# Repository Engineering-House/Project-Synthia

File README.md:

# Project Synthia
Project Synthia is a digital synthesizer that is designed based upon the Suzuki Omnichord. This repository contains the firmware code for the microcontroller as well as the hardware schematics.

# Project Synthia Firmware

A brief description of what this firmware does, the target application, and the primary protocol used (e.g., "An ESP32-based firmware for monitoring soil moisture via MQTT").

## Hardware Requirements

* **Microcontroller:** [e.g., STM32F405RG / ESP32-WROOM-32E]
* **Development Board/PCB:** NUCLEO-G431KB
* **External Peripherals:** 
* **Debugger/Programmer:**

### Pin Mapping
The pins are mapped to the following variable values. It is currently understood that on the NUCLEO-G431KB, the PB9 pin does not exist.

| Variable | Pin | Pin Type | IO |
| :--- | :--- | :--- | :--- |
| majorChords | PA7 | GPIO | Output |
| minorChords | PB0 | GPIO | Output |
| seventhChords | PA9 | GPIO | Output |
| DAC_0 | PF0 | GPIO | Output |
| DAC_1 | PF1 | GPIO | Output |
| DAC_2 | PA8 | GPIO | Output |
| DAC_3 | PA0 | GPIO | Output |
| DAC_4 | PA1 | GPIO | Output |
| DAC_5 | PA4 | GPIO | Output |
| DAC_6 | PA5 | GPIO | Output |
| DAC_7 | PA6 | GPIO | Output |
| tempoControl | PB9 | Analog | Input |
| rhythmSwitch | PA10 | GPIO | Input |
| rhythmMatrix[4] | PA11 | GPIO | Input |
| fontSwitch | PA12 | GPIO | Input |
| fontMatrix[4] | PA15 | GPIO | Input |
| chordMatrix_0 | PB4 | GPIO | Input |
| chordMatrix_1 | PB5 | GPIO | Input |
| chordMatrix_2 | PB6 | GPIO | Input |
| chordMatrix_3 | PB7 | GPIO | Input |

## Getting Started

### Prerequisites & Toolchain
* **IDE/Framework:** STM32CubeIDE, STM32CubeMX
* **Compiler:** 
* **Dependencies:** N/A

### Building the Firmware
```bash
# Clone the repository
git clone https://github.com/Engineering-House/Project-Synthia.git
cd Project-Synthia/Synthia-Firmware
```

In the STM32CubeIDE, after opening the firmware folder detailed above, clean and build the project from the Project menu.

##  Flashing & Debugging

There is currently no flashing and debugging process. Please update this when needed.

## Configuration

Explain how users can modify settings before compiling (e.g., Wi-Fi credentials, baud rates, calibration constants).
* **Configuration File:** 
* **Key Parameters:**
## Testing & Debugging

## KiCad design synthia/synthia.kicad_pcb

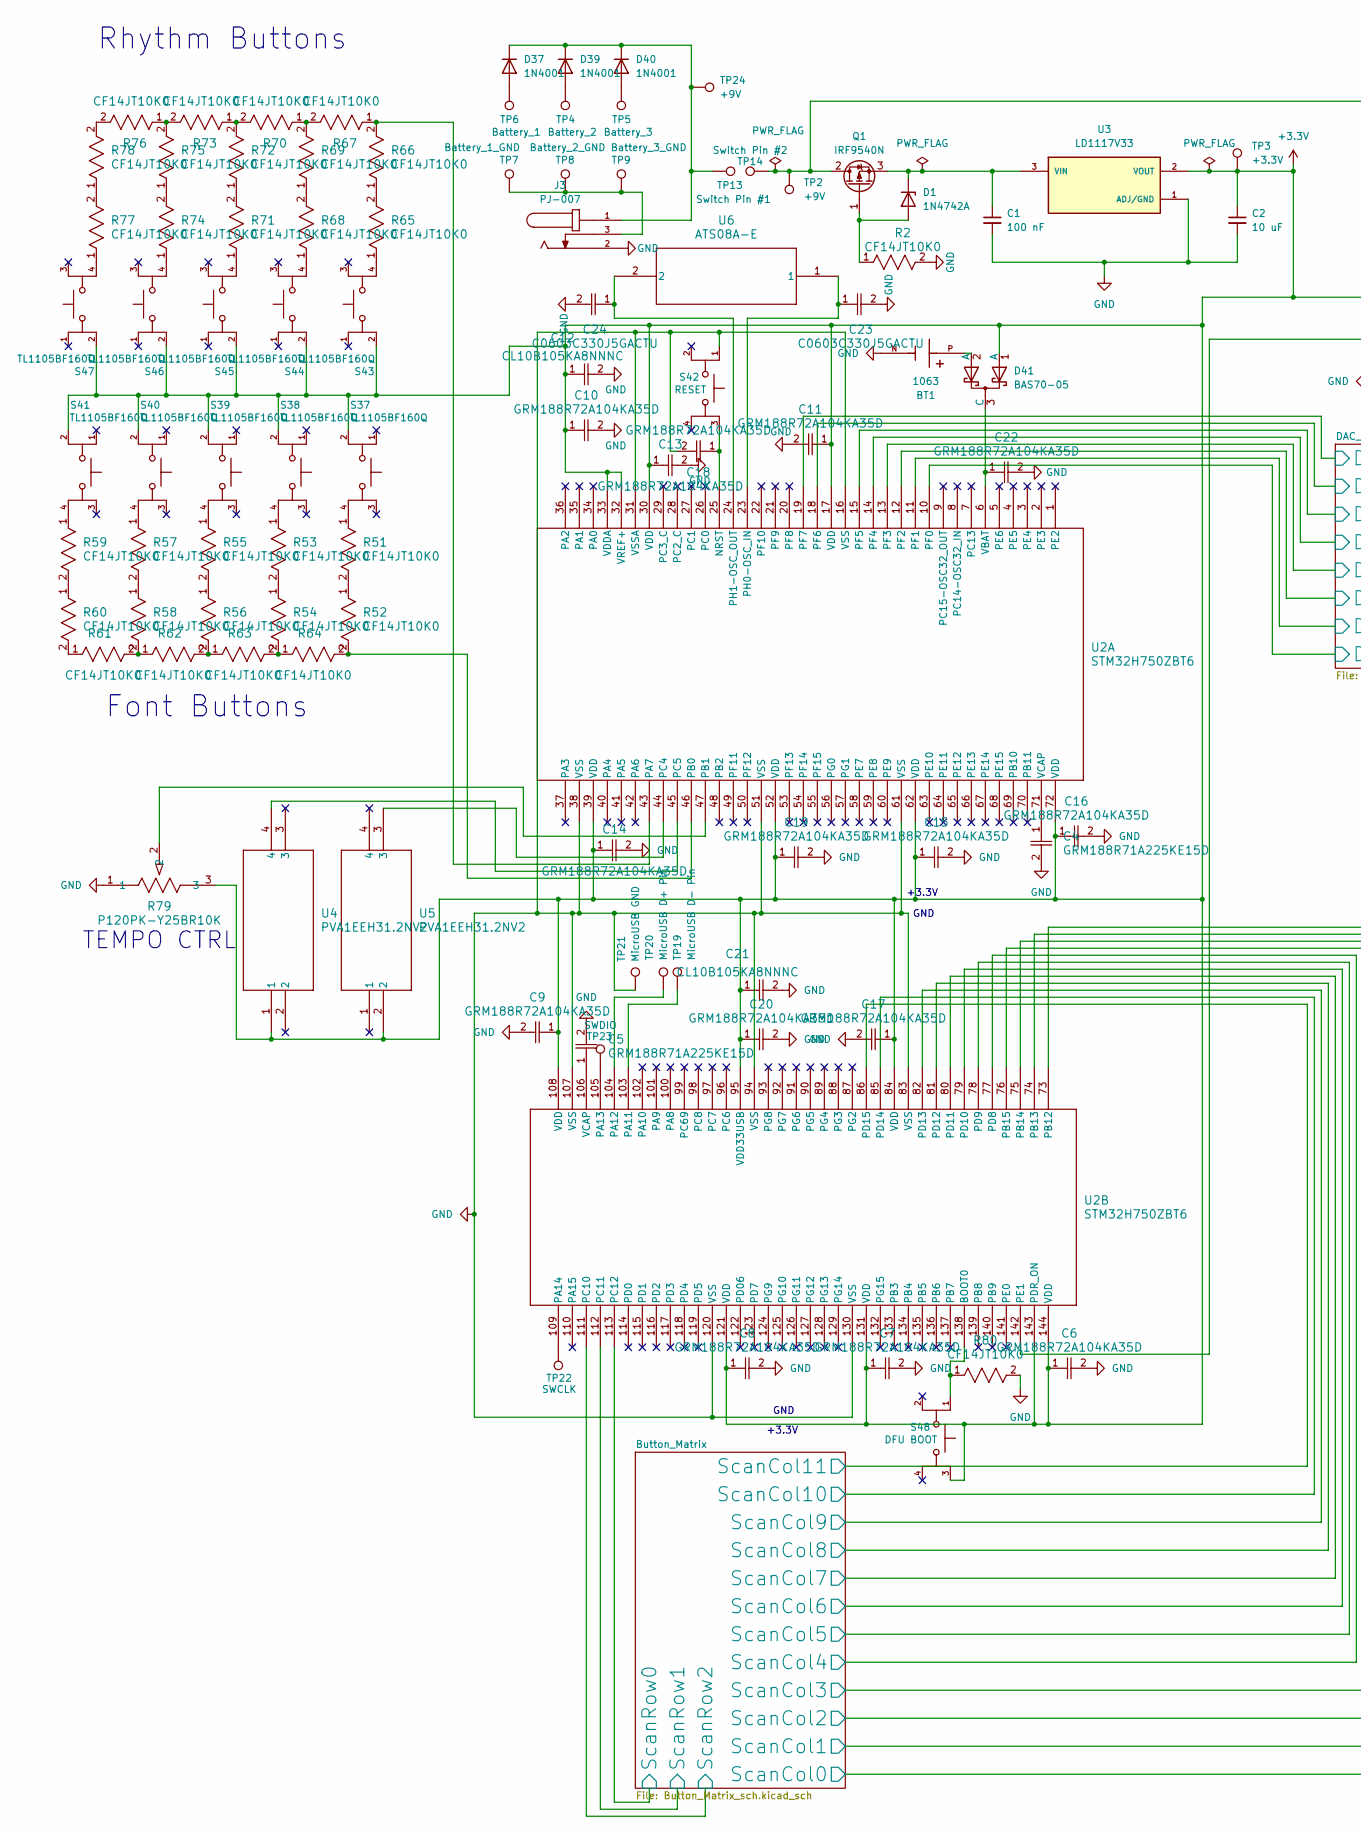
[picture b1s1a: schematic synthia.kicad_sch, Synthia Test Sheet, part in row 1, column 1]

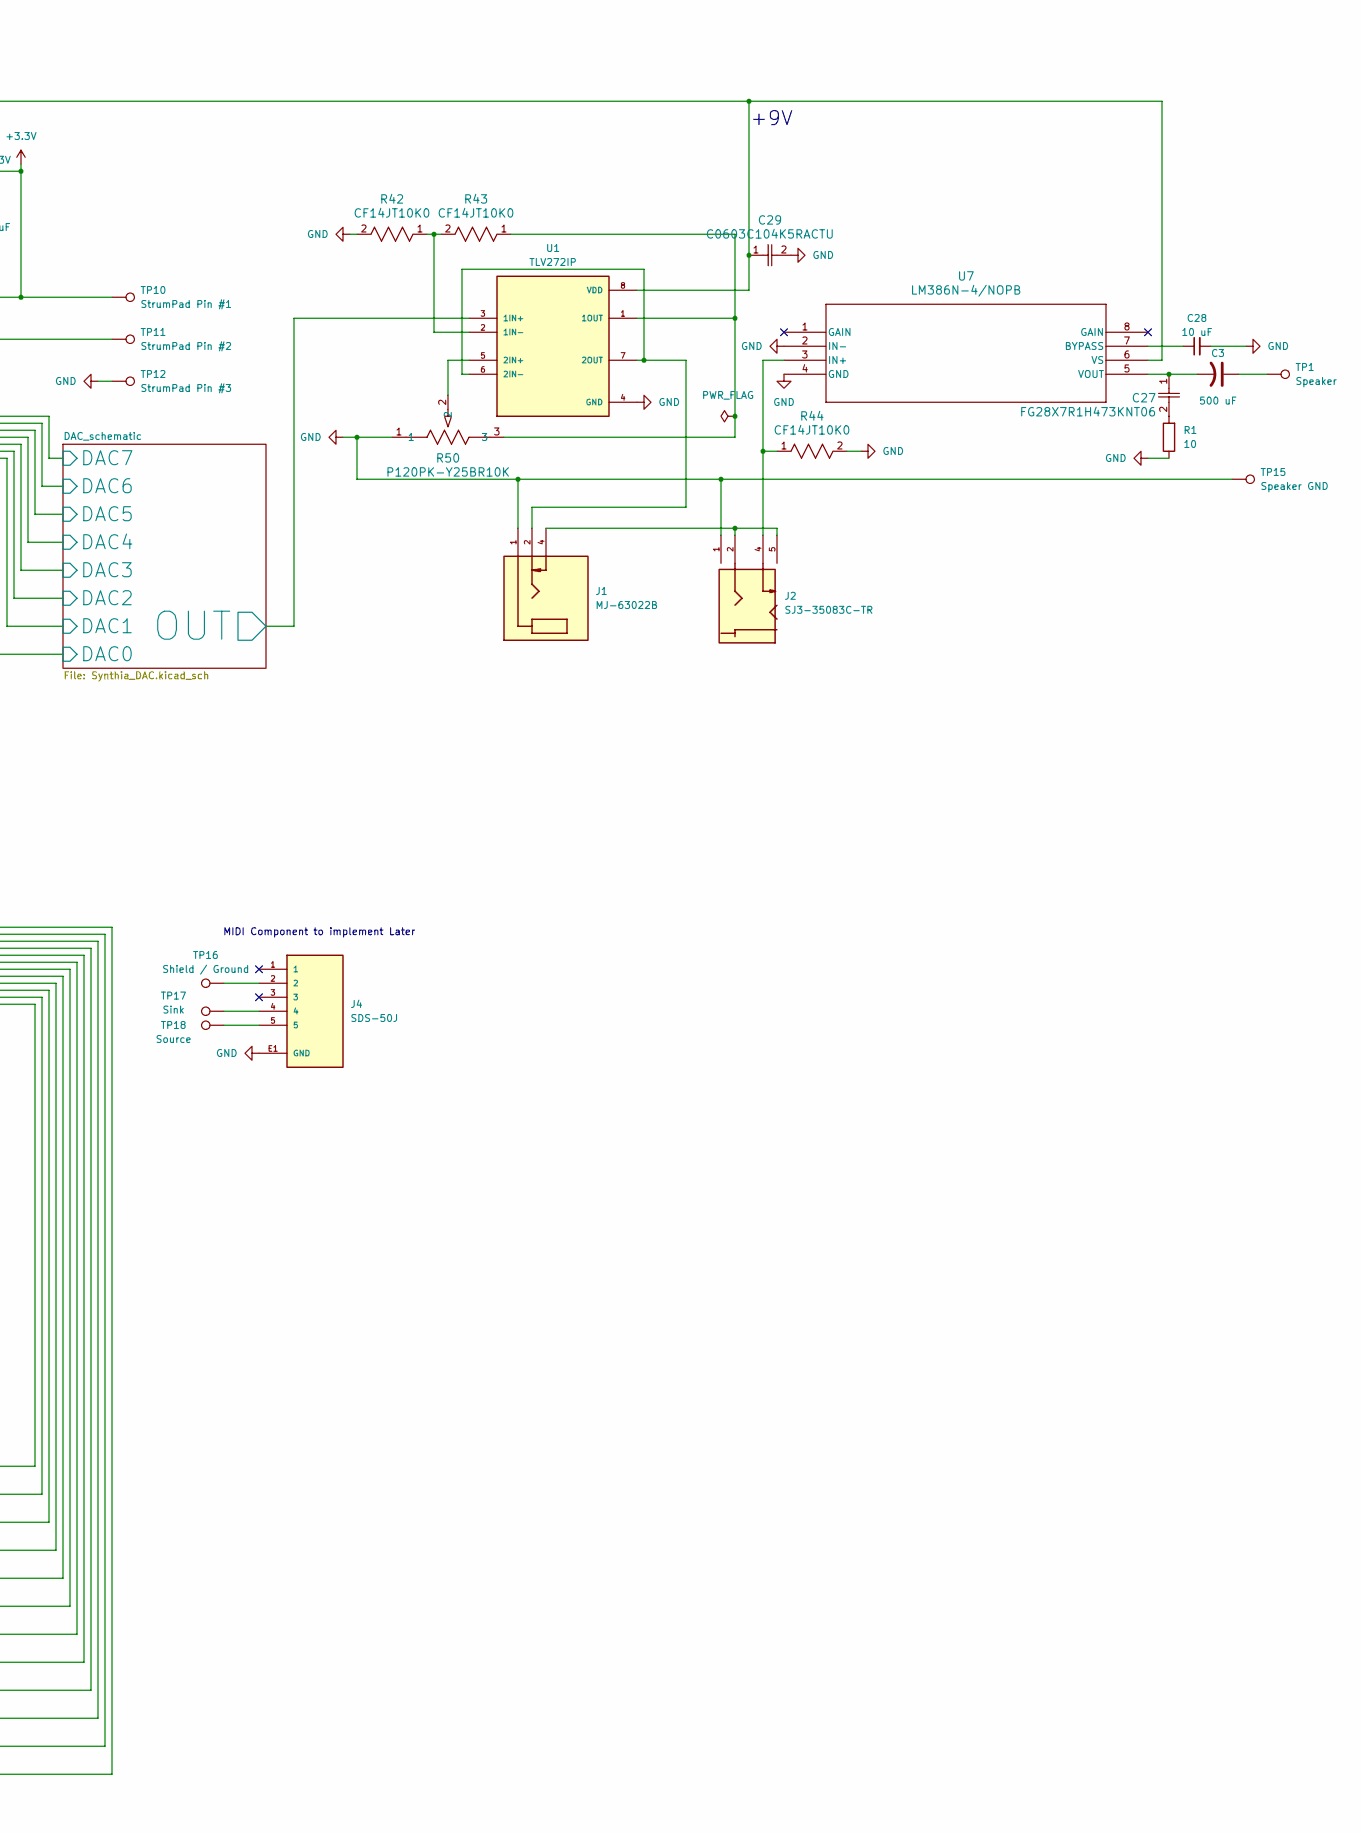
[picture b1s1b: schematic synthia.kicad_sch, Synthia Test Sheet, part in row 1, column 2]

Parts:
BT1: 1063; BAT_1063; PARTREV F
C1: 100 nF; CP_Radial_Tantal_D5.0mm_P5.00mm
C2, C28: 10 uF; CP_Radial_Tantal_D5.0mm_P5.00mm
C3: 500 uF; CP_Radial_Tantal_D5.0mm_P5.00mm
C4, C5: GRM188R71A225KE15D; G-188_MUR
C6, C7, C8, C9, C10, C11, C13, C14, C15, C16, C17, C18, C19, C20, C22: GRM188R72A104KA35D
C12, C21: CL10B105KA8NNNC; CAP_CL10_SAM-L
C23, C24: C0603C330J5GACTU; CAPC17595_87N_KEM-L
C27: FG28X7R1H473KNT06; CAP_FG28_TDK
C29: C0603C104K5RACTU; CAPC17595_95N_KEM-L
D1: 1N4742A; D_DO-41_SOD81_P10.16mm_Horizontal
D37, D39, D40: 1N4001; D_DO-41_SOD81_P10.16mm_Horizontal
D41: BAS70-05; P200_SOT-23
J1: MJ-63022B; CUI_MJ-63022B; PARTREV 1.0
J2: SJ3-35083C-TR; SAMESKY_SJ3-35083C-TR; PARTREV 1.01
J3: PJ-007; SAMESKY_PJ-007; PARTREV 1.07
J4: SDS-50J; CUI_SDS-50J; PARTREV 1.06/02-13-2020
Q1: IRF9540N; TO-220-3_Vertical
R1: 10; STA_CF14_STP
R2, R42, R43, R44, R51, R52, R53, R54, R55, R56, R57, R58, R59, R60, R61, R62, R63, R64, R65, R66, R67, R68, R69, R70, R71, R72, R73, R74, R75, R76, R77, R78, R80: CF14JT10K0; STA_CF14_STP
R50, R79: P120PK-Y25BR10K; POT_P120PK-x25_TTE
S37, S38, S39, S40, S41, S43, S44, S45, S46, S47: TL1105BF160Q; SW_TL1105BF160Q; PARTREV A
S42: RESET; SW_TL1105BF160Q; PARTREV A
S48: DFU BOOT; SW_TL1105BF160Q; PARTREV A
TP1: Speaker; TestPoint_Plated_Hole_D2.0mm
TP2, TP24: +9V; TestPoint_Pad_2.0x2.0mm
TP3: +3.3V; TestPoint_Pad_2.0x2.0mm
TP4: Battery_2; TestPoint_Plated_Hole_D2.0mm
TP5: Battery_3; TestPoint_Plated_Hole_D2.0mm
TP6: Battery_1; TestPoint_Plated_Hole_D2.0mm
TP7: Battery_1_GND; TestPoint_Plated_Hole_D2.0mm
TP8: Battery_2_GND; TestPoint_Plated_Hole_D2.0mm
TP9: Battery_3_GND; TestPoint_Plated_Hole_D2.0mm
TP10: StrumPad Pin #1; TestPoint_Plated_Hole_D2.0mm
TP11: StrumPad Pin #2; TestPoint_Plated_Hole_D2.0mm
TP12: StrumPad Pin #3; TestPoint_Plated_Hole_D2.0mm
TP13: Switch Pin #1; TestPoint_Plated_Hole_D2.0mm
TP14: Switch Pin #2; TestPoint_Plated_Hole_D2.0mm
TP15: Speaker GND; TestPoint_Plated_Hole_D2.0mm
TP16: Shield / Ground; TestPoint_Plated_Hole_D2.0mm
TP17: Sink; TestPoint_Plated_Hole_D2.0mm
TP18: Source; TestPoint_Plated_Hole_D2.0mm
TP19: MicroUSB D- Pin; TestPoint_Plated_Hole_D2.0mm
TP20: MicroUSB D+ Pin; TestPoint_Plated_Hole_D2.0mm
TP21: MicroUSB GND; TestPoint_Plated_Hole_D2.0mm
TP22: SWCLK; TestPoint_Plated_Hole_D2.0mm
TP23: SWDIO; TestPoint_Plated_Hole_D2.0mm
U1: TLV272IP; DIP794W45P254L959H508Q8; PARTREV E
U2: STM32H750ZBT6; LQFP144_STM
U3: LD1117V33; TO255P1020X450X1968-3; PARTREV 37
U4, U5: PVA1EEH31.2NV2; SWITCH_H31.2NV2
U6: ATS08A-E; ATS08A-E_CTS
U7: LM386N-4/NOPB; N08E_TEX

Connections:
+3.3V: C2.1, C6.1, C7.1, C8.1, C9.1, C10.1, C11.1, C12.1, C13.1, C14.1, C15.1, C16.1, C17.1, C19.1, C20.1, C21.1, D41.1 (A), R79.3, S37.2, S38.2, S39.2, S40.2, S41.2, S43.2, S44.2, S45.2, S46.2, S47.2, S48.3, TP3.1 (1_1), TP10.1 (1_1), U2.17 (VDD), U2.30 (VDD), U2.32 (VREF+), U2.33 (VDDA), U2.39 (VDD), U2.52 (VDD), U2.62 (VDD), U2.72 (VDD), U2.84 (VDD), U2.95 (VDD33USB), U2.108 (VDD), U2.121 (VDD), U2.131 (VDD), U2.143 (PDR_ON), U2.144 (VDD), U3.2 (VOUT), U4.1, U5.2
/Button_Matrix/ScanCol0: U2.73 (PB12); also elsewhere on the board
/Button_Matrix/ScanCol1: U2.74 (PB13); also elsewhere on the board
/Button_Matrix/ScanCol2: U2.75 (PB14); also elsewhere on the board
/Button_Matrix/ScanCol3: U2.76 (PB15); also elsewhere on the board
/Button_Matrix/ScanCol4: U2.77 (PD8); also elsewhere on the board
/Button_Matrix/ScanCol5: U2.78 (PD9); also elsewhere on the board
/Button_Matrix/ScanCol6: U2.79 (PD10); also elsewhere on the board
/Button_Matrix/ScanCol7: U2.80 (PD11); also elsewhere on the board
/Button_Matrix/ScanCol8: U2.81 (PD12); also elsewhere on the board
/Button_Matrix/ScanCol9: U2.82 (PD13); also elsewhere on the board
/Button_Matrix/ScanCol10: U2.85 (PD14); also elsewhere on the board
/Button_Matrix/ScanCol11: U2.86 (PD15); also elsewhere on the board
/Button_Matrix/ScanRow0: U2.113 (PC12); also elsewhere on the board
/Button_Matrix/ScanRow1: U2.112 (PC11); also elsewhere on the board
/Button_Matrix/ScanRow2: U2.111 (PC10); also elsewhere on the board
/DAC_schematic/DAC0: U2.10 (PF0); also elsewhere on the board
/DAC_schematic/DAC1: U2.11 (PF1); also elsewhere on the board
/DAC_schematic/DAC2: U2.12 (PF2); also elsewhere on the board
/DAC_schematic/DAC3: U2.13 (PF3); also elsewhere on the board
/DAC_schematic/DAC4: U2.14 (PF4); also elsewhere on the board
/DAC_schematic/DAC5: U2.15 (PF5); also elsewhere on the board
/DAC_schematic/DAC6: U2.18 (PF6); also elsewhere on the board
/DAC_schematic/DAC7: U2.19 (PF7); also elsewhere on the board
/DAC_schematic/OUT: U1.3 (1IN+); also elsewhere on the board
GND: BT1.N, C1.2, C2.2, C4.2, C5.2, C6.2, C7.2, C8.2, C9.2, C10.2, C11.2, C12.2, C13.2, C14.2, C15.2, C16.2, C17.2, C18.2, C19.2, C20.2, C21.2, C22.2, C23.2, C24.2, C28.2, C29.2, J1.1, J2.1, J3.2, J4.E1 (GND), J4.E2 (GND), R1.1, R2.2, R42.2, R44.2, R50.1, R79.1, R80.2, S42.1, TP12.1 (1_1), TP15.1 (1_1), TP21.1 (1_1), U1.4 (GND), U2.16 (VSS), U2.31 (VSSA), U2.38 (VSS), U2.51 (VSS), U2.61 (VSS), U2.83 (VSS), U2.94 (VSS), U2.107 (VSS), U2.120 (VSS), U2.130 (VSS), U3.1 (ADJ/GND), U7.2 (IN-), U7.4 (GND); also elsewhere on the board
unnamed: BT1.P, D41.2 (A)
unnamed: C3.1, TP1.1 (1_1)
unnamed: C27.2, R1.2
unnamed: D1.2 (A), Q1.1 (G), R2.1
unnamed: C1.1, D1.1 (K), Q1.3 (S), U3.3 (VIN)
unnamed: D37.2 (A), TP6.1 (1_1)
unnamed: D37.1 (K), D39.1 (K), D40.1 (K), J3.1, TP13.1 (1_1), TP24.1 (1_1)
unnamed: D39.2 (A), TP4.1 (1_1)
unnamed: D40.2 (A), TP5.1 (1_1)
unnamed: C22.1, D41.3 (C), U2.6 (VBAT)
unnamed: J1.4, J2.2, J2.5
unnamed: J3.3, TP7.1 (1_1), TP8.1 (1_1), TP9.1 (1_1)
unnamed: J4.2, TP16.1 (1_1)
unnamed: J4.4, TP17.1 (1_1)
unnamed: J4.5, TP18.1 (1_1)
unnamed: C29.1, Q1.2 (D), TP2.1 (1_1), TP14.1 (1_1), U1.8 (VDD), U7.6 (VS)
unnamed: R51.1, S37.4
unnamed: R51.2, R52.1
unnamed: R53.1, S38.4
unnamed: R53.2, R54.1
unnamed: R54.2, R63.2, R64.1
unnamed: R55.1, S39.4
unnamed: R55.2, R56.1
unnamed: R56.2, R62.2, R63.1
unnamed: R57.1, S40.4
unnamed: R57.2, R58.1
unnamed: R58.2, R61.2, R62.1
unnamed: R59.1, S41.4
unnamed: R59.2, R60.1
unnamed: R60.2, R61.1
unnamed: R65.1, S43.4
unnamed: R65.2, R66.1
unnamed: R67.2, R69.2, R70.1
unnamed: R68.1, S44.4
unnamed: R68.2, R69.1
unnamed: R70.2, R72.2, R73.1
unnamed: R71.1, S45.4
unnamed: R71.2, R72.1
unnamed: R73.2, R75.2, R76.1
unnamed: R74.1, S46.4
unnamed: R74.2, R75.1
unnamed: R76.2, R78.2
unnamed: R77.1, S47.4
unnamed: R77.2, R78.1
unnamed: R42.1, R43.2, U1.2 (1IN-)
unnamed: R43.1, R50.3, U1.1 (1OUT)
unnamed: R50.2, U1.5 (2IN+)
unnamed: J1.2, U1.6 (2IN-), U1.7 (2OUT)
unnamed: C18.1, S42.3, U2.25 (NRST)
unnamed: R66.2, R67.1, U2.43 (PA7)
unnamed: R52.2, R64.2, U2.46 (PB0)
unnamed: R79.2, U2.47 (PB1)
unnamed: U2.44 (PC4), U5.3
unnamed: U2.45 (PC5), U4.4
unnamed: C23.1, U2.23 (PH0-OSC_IN), U6.1
unnamed: C24.1, U2.24 (PH1-OSC_OUT), U6.2
unnamed: C4.1, U2.71 (VCAP)
unnamed: R80.1, S48.1, U2.138 (BOOT0)
unnamed: TP19.1 (1_1), U2.103 (PA11)
unnamed: TP20.1 (1_1), U2.104 (PA12)
unnamed: TP23.1 (1_1), U2.105 (PA13)
unnamed: TP22.1 (1_1), U2.109 (PA14)
unnamed: TP11.1 (1_1), U2.142 (PE1)
unnamed: C5.1, U2.106 (VCAP)
unnamed: C28.1, U7.7 (BYPASS)
unnamed: J2.4, R44.1, U7.3 (IN+)
unnamed: C3.2, C27.1, U7.5 (VOUT)

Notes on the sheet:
+3.3V
+9V
GND
TEMPO CTRL
MIDI Component to implement Later
Font Buttons
Rhythm Buttons

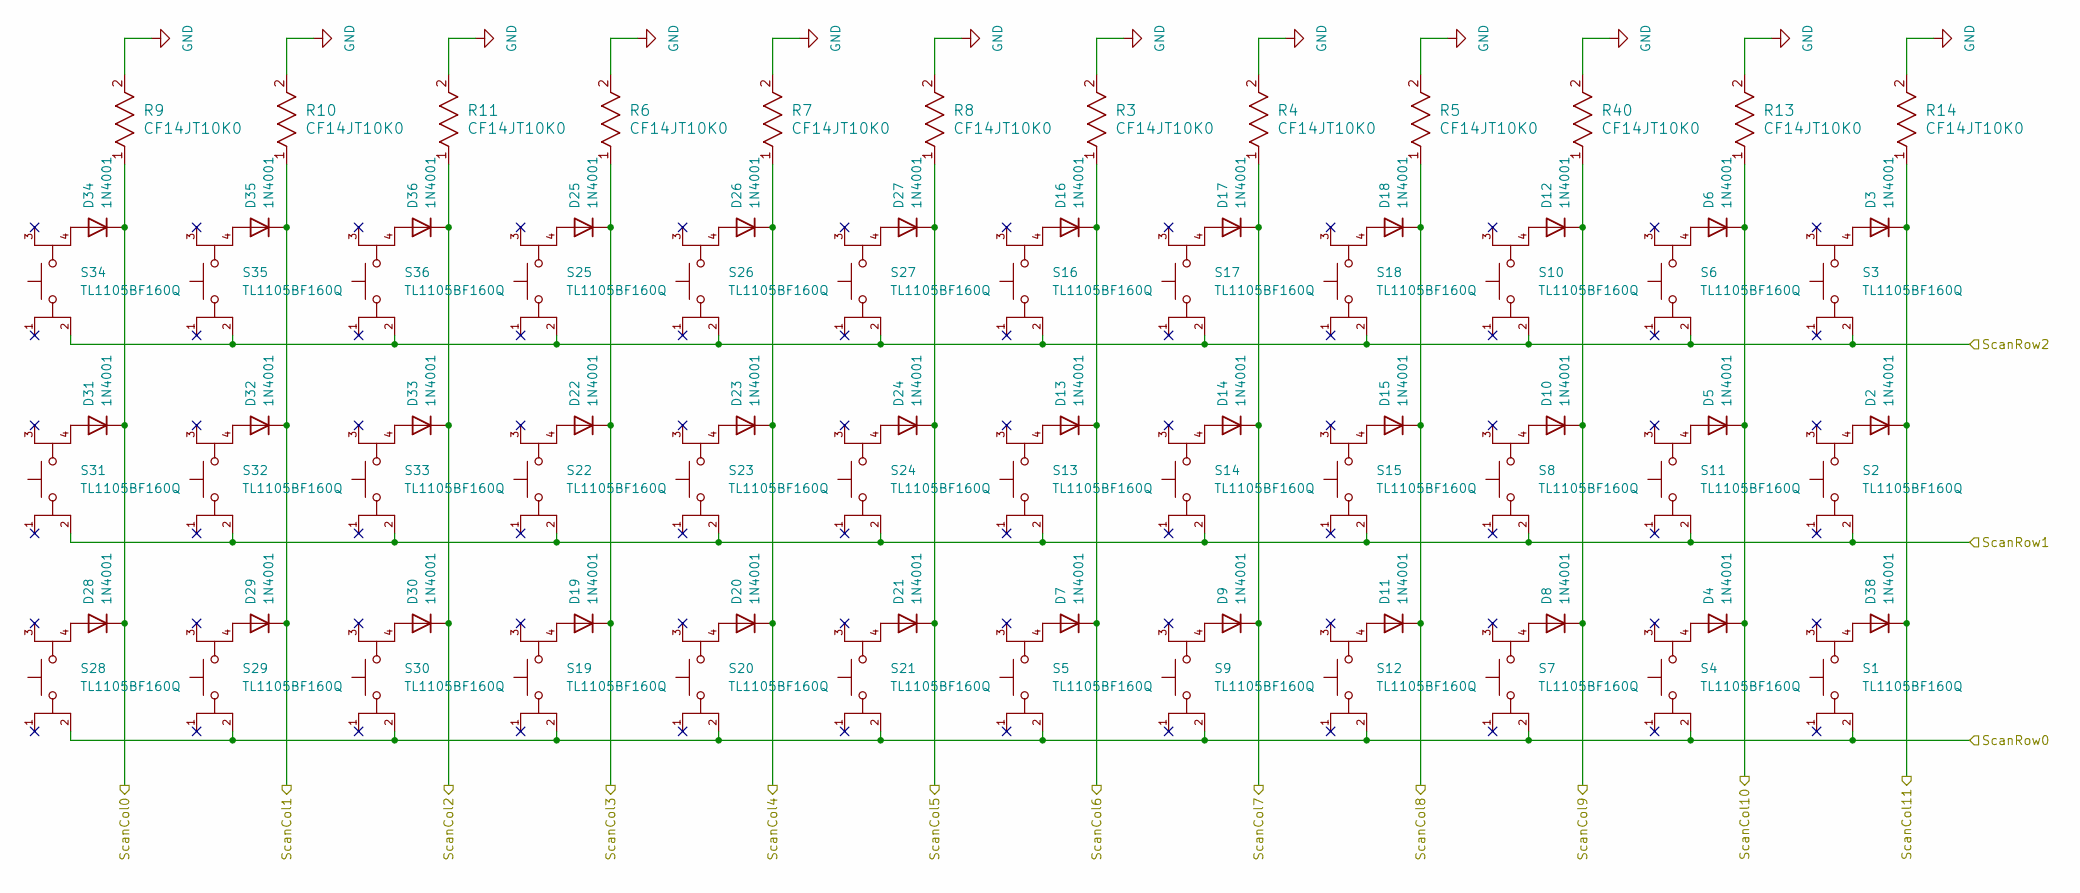
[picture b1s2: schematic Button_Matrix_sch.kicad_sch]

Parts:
D2, D3, D4, D5, D6, D7, D8, D9, D10, D11, D12, D13, D14, D15, D16, D17, D18, D19, D20, D21, D22, D23, D24, D25, D26, D27, D28, D29, D30, D31, D32, D33, D34, D35, D36, D38: 1N4001; D_DO-41_SOD81_P10.16mm_Horizontal
R3, R4, R5, R6, R7, R8, R9, R10, R11, R13, R14, R40: CF14JT10K0; STA_CF14_STP
S1, S2, S3, S4, S5, S6, S7, S8, S9, S10, S11, S12, S13, S14, S15, S16, S17, S18, S19, S20, S21, S22, S23, S24, S25, S26, S27, S28, S29, S30, S31, S32, S33, S34, S35, S36: TL1105BF160Q; SW_TL1105BF160Q; PARTREV A

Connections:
/Button_Matrix/ScanCol0: D28.1 (K), D31.1 (K), D34.1 (K), R9.1; also elsewhere on the board
/Button_Matrix/ScanCol1: D29.1 (K), D32.1 (K), D35.1 (K), R10.1; also elsewhere on the board
/Button_Matrix/ScanCol2: D30.1 (K), D33.1 (K), D36.1 (K), R11.1; also elsewhere on the board
/Button_Matrix/ScanCol3: D19.1 (K), D22.1 (K), D25.1 (K), R6.1; also elsewhere on the board
/Button_Matrix/ScanCol4: D20.1 (K), D23.1 (K), D26.1 (K), R7.1; also elsewhere on the board
/Button_Matrix/ScanCol5: D21.1 (K), D24.1 (K), D27.1 (K), R8.1; also elsewhere on the board
/Button_Matrix/ScanCol6: D7.1 (K), D13.1 (K), D16.1 (K), R3.1; also elsewhere on the board
/Button_Matrix/ScanCol7: D9.1 (K), D14.1 (K), D17.1 (K), R4.1; also elsewhere on the board
/Button_Matrix/ScanCol8: D11.1 (K), D15.1 (K), D18.1 (K), R5.1; also elsewhere on the board
/Button_Matrix/ScanCol9: D8.1 (K), D10.1 (K), D12.1 (K), R40.1; also elsewhere on the board
/Button_Matrix/ScanCol10: D4.1 (K), D5.1 (K), D6.1 (K), R13.1; also elsewhere on the board
/Button_Matrix/ScanCol11: D2.1 (K), D3.1 (K), D38.1 (K), R14.1; also elsewhere on the board
/Button_Matrix/ScanRow0: S1.2, S4.2, S5.2, S7.2, S9.2, S12.2, S19.2, S20.2, S21.2, S28.2, S29.2, S30.2; also elsewhere on the board
/Button_Matrix/ScanRow1: S2.2, S8.2, S11.2, S13.2, S14.2, S15.2, S22.2, S23.2, S24.2, S31.2, S32.2, S33.2; also elsewhere on the board
/Button_Matrix/ScanRow2: S3.2, S6.2, S10.2, S16.2, S17.2, S18.2, S25.2, S26.2, S27.2, S34.2, S35.2, S36.2; also elsewhere on the board
GND: R3.2, R4.2, R5.2, R6.2, R7.2, R8.2, R9.2, R10.2, R11.2, R13.2, R14.2, R40.2; also elsewhere on the board
unnamed: D2.2 (A), S2.4
unnamed: D3.2 (A), S3.4
unnamed: D4.2 (A), S4.4
unnamed: D5.2 (A), S11.4
unnamed: D6.2 (A), S6.4
unnamed: D7.2 (A), S5.4
unnamed: D8.2 (A), S7.4
unnamed: D9.2 (A), S9.4
unnamed: D10.2 (A), S8.4
unnamed: D11.2 (A), S12.4
unnamed: D12.2 (A), S10.4
unnamed: D13.2 (A), S13.4
unnamed: D14.2 (A), S14.4
unnamed: D15.2 (A), S15.4
unnamed: D16.2 (A), S16.4
unnamed: D17.2 (A), S17.4
unnamed: D18.2 (A), S18.4
unnamed: D19.2 (A), S19.4
unnamed: D20.2 (A), S20.4
unnamed: D21.2 (A), S21.4
unnamed: D22.2 (A), S22.4
unnamed: D23.2 (A), S23.4
unnamed: D24.2 (A), S24.4
unnamed: D25.2 (A), S25.4
unnamed: D26.2 (A), S26.4
unnamed: D27.2 (A), S27.4
unnamed: D28.2 (A), S28.4
unnamed: D29.2 (A), S29.4
unnamed: D30.2 (A), S30.4
unnamed: D31.2 (A), S31.4
unnamed: D32.2 (A), S32.4
unnamed: D33.2 (A), S33.4
unnamed: D34.2 (A), S34.4
unnamed: D35.2 (A), S35.4
unnamed: D36.2 (A), S36.4
unnamed: D38.2 (A), S1.4

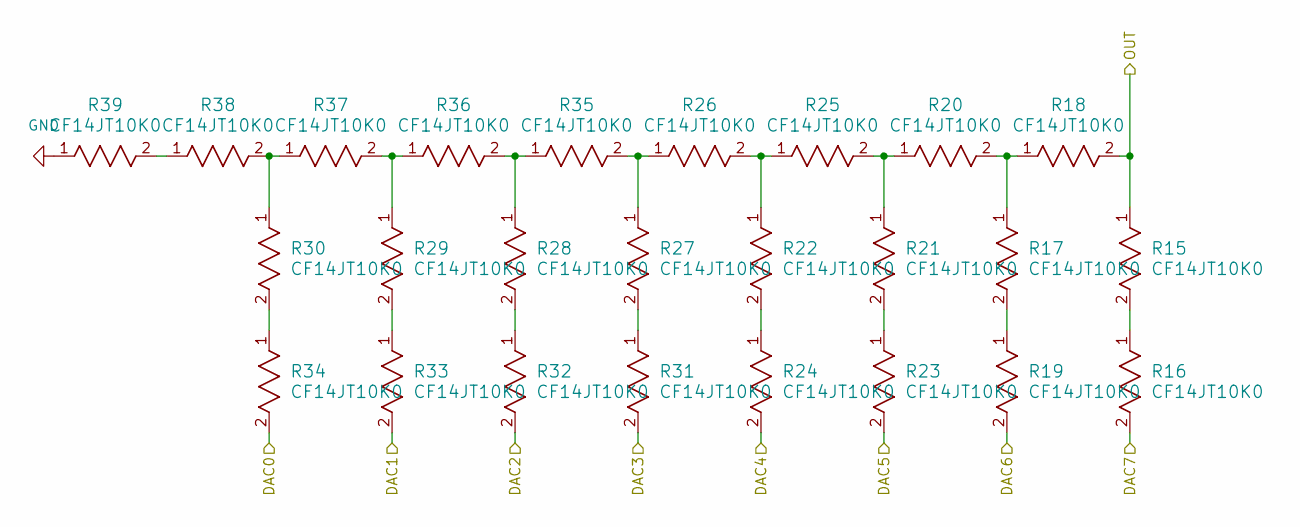
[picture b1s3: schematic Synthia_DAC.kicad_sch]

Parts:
R15, R16, R17, R18, R19, R20, R21, R22, R23, R24, R25, R26, R27, R28, R29, R30, R31, R32, R33, R34, R35, R36, R37, R38, R39: CF14JT10K0; STA_CF14_STP

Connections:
/DAC_schematic/DAC0: R34.2; also elsewhere on the board
/DAC_schematic/DAC1: R33.2; also elsewhere on the board
/DAC_schematic/DAC2: R32.2; also elsewhere on the board
/DAC_schematic/DAC3: R31.2; also elsewhere on the board
/DAC_schematic/DAC4: R24.2; also elsewhere on the board
/DAC_schematic/DAC5: R23.2; also elsewhere on the board
/DAC_schematic/DAC6: R19.2; also elsewhere on the board
/DAC_schematic/DAC7: R16.2; also elsewhere on the board
/DAC_schematic/OUT: R15.1, R18.2; also elsewhere on the board
GND: R39.1; also elsewhere on the board
unnamed: R15.2, R16.1
unnamed: R17.1, R18.1, R20.2
unnamed: R17.2, R19.1
unnamed: R20.1, R21.1, R25.2
unnamed: R21.2, R23.1
unnamed: R22.1, R25.1, R26.2
unnamed: R22.2, R24.1
unnamed: R26.1, R27.1, R35.2
unnamed: R27.2, R31.1
unnamed: R28.1, R35.1, R36.2
unnamed: R28.2, R32.1
unnamed: R29.1, R36.1, R37.2
unnamed: R29.2, R33.1
unnamed: R30.1, R37.1, R38.2
unnamed: R30.2, R34.1
unnamed: R38.1, R39.2

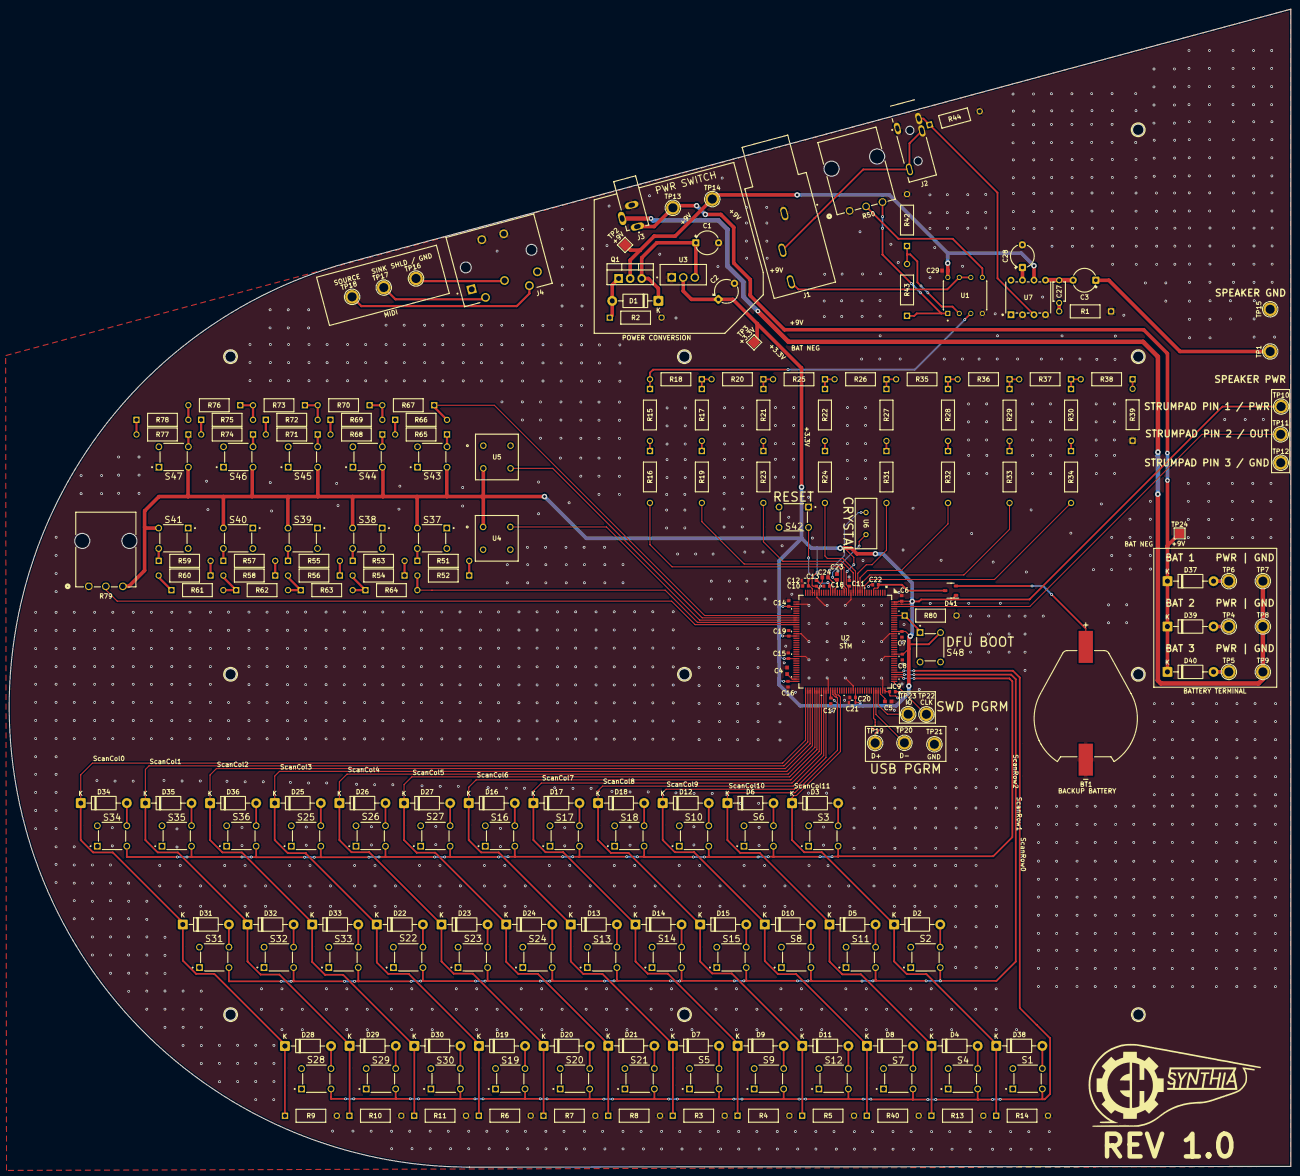
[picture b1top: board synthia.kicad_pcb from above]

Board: 2 copper layers, 282.4 x 255.2 mm, 227 parts (0 on the bottom side), 145 nets.

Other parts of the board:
LOGO: LOGO

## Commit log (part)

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2026-03-01 KiCad .gitignore file
2026-03-01 Test project files
2026-03-01 Meaningful Commit Message (Test)
2026-03-01 This has the power part made out k
2026-03-02 Testing adding a file to the repository
2026-03-15 Stuff from this meeting
2026-03-25 Ayo this is Anthony Bruno commiting to Synthia. I'm Synthing it!
2026-03-26 updated with new symbols
2026-03-26 Symbols for Button and Op Amp
2026-03-26 Embedded DAC and Button Matrix into IC style subsheets (Not Documented
2026-03-26 small edit to the Button Matrix schematic
2026-03-26 deleted old test file
2026-03-29 Started on the PCB, button matrix is active
2026-04-02 More PCB Updates for the Matrix
2026-04-09 Output circuit has been made into a schematic
2026-04-15 STM init
2026-04-16 More updates to the Schematic, implemented some of the ports that will be on the pcb
2026-04-16 Made changes to the schematic to implement some ports
2026-04-18 More updates to the Schematic, ports and solder points added for external components and were wired up
2026-04-19 More updates to Schematic, added latching switch as a symbol and footprint
2026-04-19 More changes made during Jank. Made a symbol and footprint for the latching switch
2026-04-25 Update README to include basic information about Project Synthia
2026-04-25 Feat: IOC UPDATE
2026-04-25 fix: duplicate file cleanup
2026-04-25 Add ADPCM files
2026-04-25 Setup audio output for the supersaw audio file (now a c array). It is important to note that I am unsure if this even works (untested) + sleep deprivation. You know how that goes.
2026-04-25 Add Timer (TIM1)
2026-04-25 feat: chord button scanning implementation
2026-04-25 feat:regenerate code from ioc
2026-05-10 did some pcb work, initial wiring complete
2026-05-11 Continued on PCB design and wiring, cannot continue until design has been further completed
2026-05-11 added all 3D models for the footprints into the pcb design, fixed some DRC errors
2026-05-12 continued PCB Work, Power circuit is wired
2026-05-12 More PCB Work, Button Matrix fully routed and strumpad wiring done
2026-05-12 Again did more Work on the PCB, Battery terminal is wired
2026-05-13 Completely had to redesign most of the pins allocated for power and designed some of the ports that will save us from potentially bricking the stm. PCB wiring for the updated schematic is NOT DONE
2026-05-14 Updated schematic now routed on the PCB, everything should be prepped for next step
2026-05-14 slight tweak, previous commit still applies\
2026-05-14 Cosmetic changes to PCB made
2026-05-15 Organized Font and Rhythm button matrices and associated switches. Not in their final location so power and IO is not routed for them yet
2026-05-15 Scaled down the PCB to be able to fit inside the 3 model case
2026-05-16 made 3D model of current PCB, will likely be updated and replaced when needed
2026-05-20 Power is pretty much fully routed, some data lines need to be routed. Final component locations established and confirmed by Jeremy and Ever.
2026-05-21 PCB Revision 1.0 complete, Ground zones are filled, all components are wired, and holes are made for standoffs for case installment. Final changes to the onshape will need to be made to accomodate th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
2026-05-21 PCB Revision 1.0 complete, Ground zones are filled, all components are wired, and holes are made for standoffs for case installment. Final changes to the onshape will need to be made to accomodate th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
